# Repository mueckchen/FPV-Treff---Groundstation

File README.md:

# FPV-Treff---Groundstation
https://www.fpv-treff.de/forum/index.php?threads/eigenbau-groundstation-videosplitter.1016/#post-31431

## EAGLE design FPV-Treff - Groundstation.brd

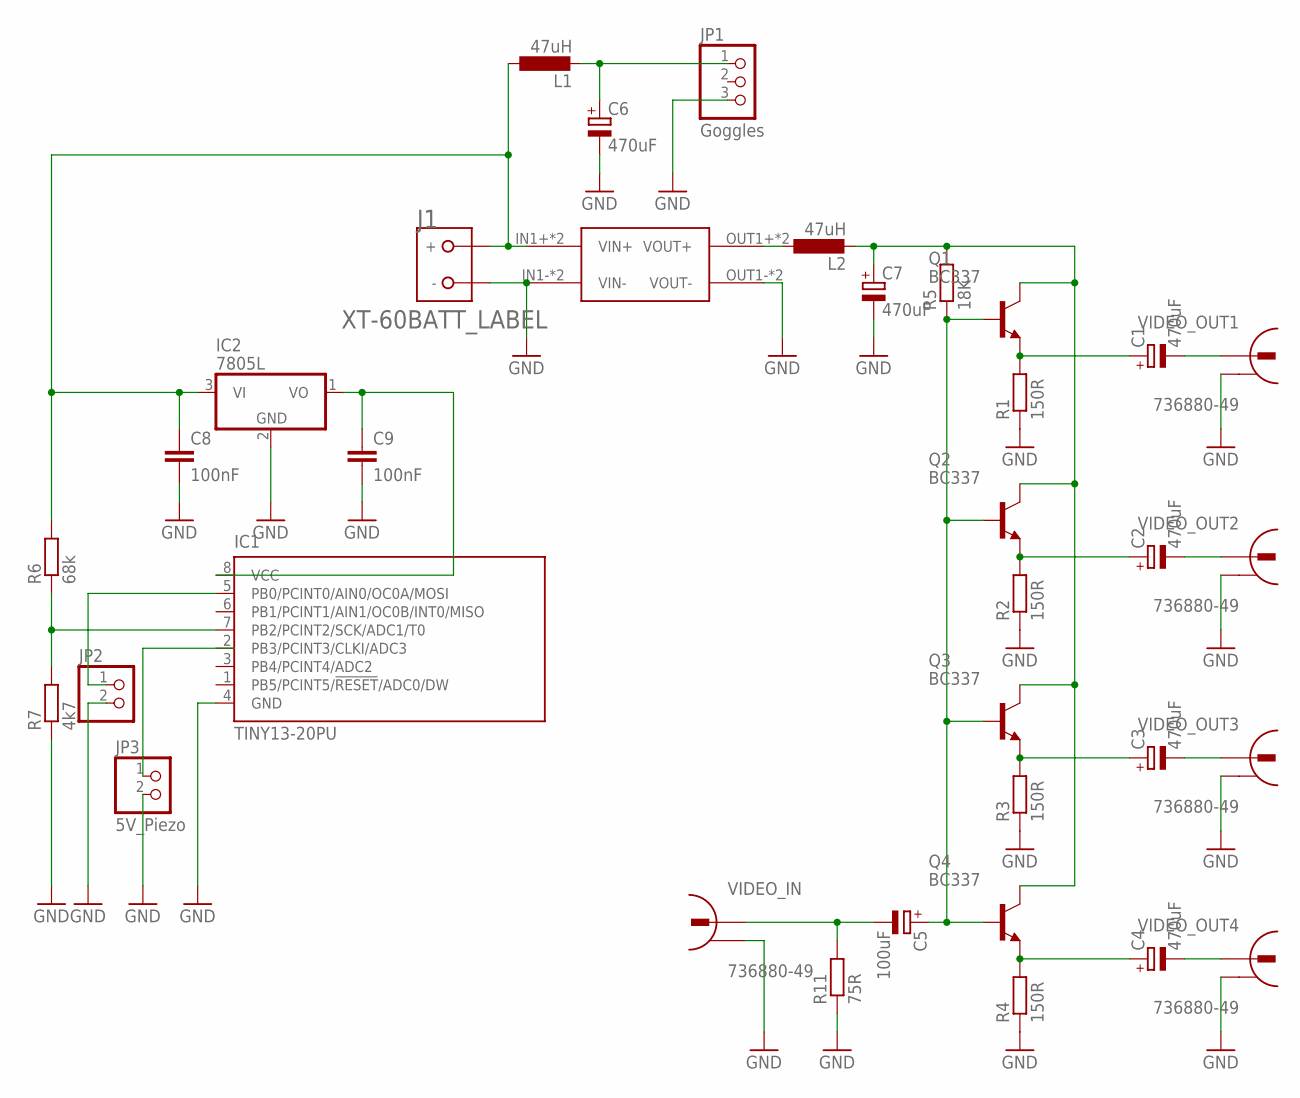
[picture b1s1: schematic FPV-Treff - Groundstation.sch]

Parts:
C1, C2, C3, C4, C6, C7: 470uF; B45181B
C5: 100uF; B45181B
C8, C9: 100nF; C025_050-025X075
IC1: TINY13-20PU; DIL08
IC2: 7805L; TO92
J1: XT-60BATT_LABEL; XT-60
JP1: Goggles; 1X03
JP2: PINHD-1X2_2.54; 1X02
JP3: 5V_Piezo; 1X02
L1, L2: 47uH; 0204V
Q1, Q2, Q3, Q4: BC337; TO92
R1, R2, R3, R4: 150R; 0204V
R5: 18K; 0204V
R6: 68k; 0207/10
R7: 4k7; 0207/10
R11: 75R; 0204V
U$1: MP1584; DC-BRICK
VIDEO_IN: 736880-49
VIDEO_OUT1, VIDEO_OUT2, VIDEO_OUT3, VIDEO_OUT4: 736880-49

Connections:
GND: C6.-, C7.-, C8.2, C9.2, IC1.4 (GND), IC2.2 (GND), J1.GND (-), JP1.3, JP2.2, JP3.2, R1.1, R2.1, R3.1, R4.1, R7.1, R11.1, U$1.IN1- (VIN-), U$1.IN2- (VIN-), U$1.OUT1- (VOUT-), U$1.OUT2- (VOUT-), VIDEO_IN.2, VIDEO_OUT1.2, VIDEO_OUT2.2, VIDEO_OUT3.2, VIDEO_OUT4.2
unnamed: C2.+, Q2.1 (E), R2.2
unnamed: C6.+, JP1.1, L1.2
unnamed: C2.-, VIDEO_OUT2.1
unnamed: C3.+, Q3.1 (E), R3.2
unnamed: C7.+, L2.2, Q1.3 (C), Q2.3 (C), Q3.3 (C), Q4.3 (C), R5.2
unnamed: C3.-, VIDEO_OUT3.1
unnamed: C8.1, IC2.3 (VI), J1.BATT (+), L1.1, R6.2, U$1.IN1+ (VIN+), U$1.IN2+ (VIN+)
unnamed: C5.-, R11.2, VIDEO_IN.1
unnamed: L2.1, U$1.OUT1+ (VOUT+), U$1.OUT2+ (VOUT+)
unnamed: IC1.5 (PB0/PCINT0/AIN0/OC0A/MOSI), JP2.1
unnamed: C9.1, IC1.8 (VCC), IC2.1 (VO)
unnamed: IC1.7 (PB2/PCINT2/SCK/ADC1/T0), R6.1, R7.2
unnamed: C1.+, Q1.1 (E), R1.2
unnamed: C4.+, Q4.1 (E), R4.2
unnamed: C5.+, Q1.2 (B), Q2.2 (B), Q3.2 (B), Q4.2 (B), R5.1
unnamed: C1.-, VIDEO_OUT1.1
unnamed: C4.-, VIDEO_OUT4.1

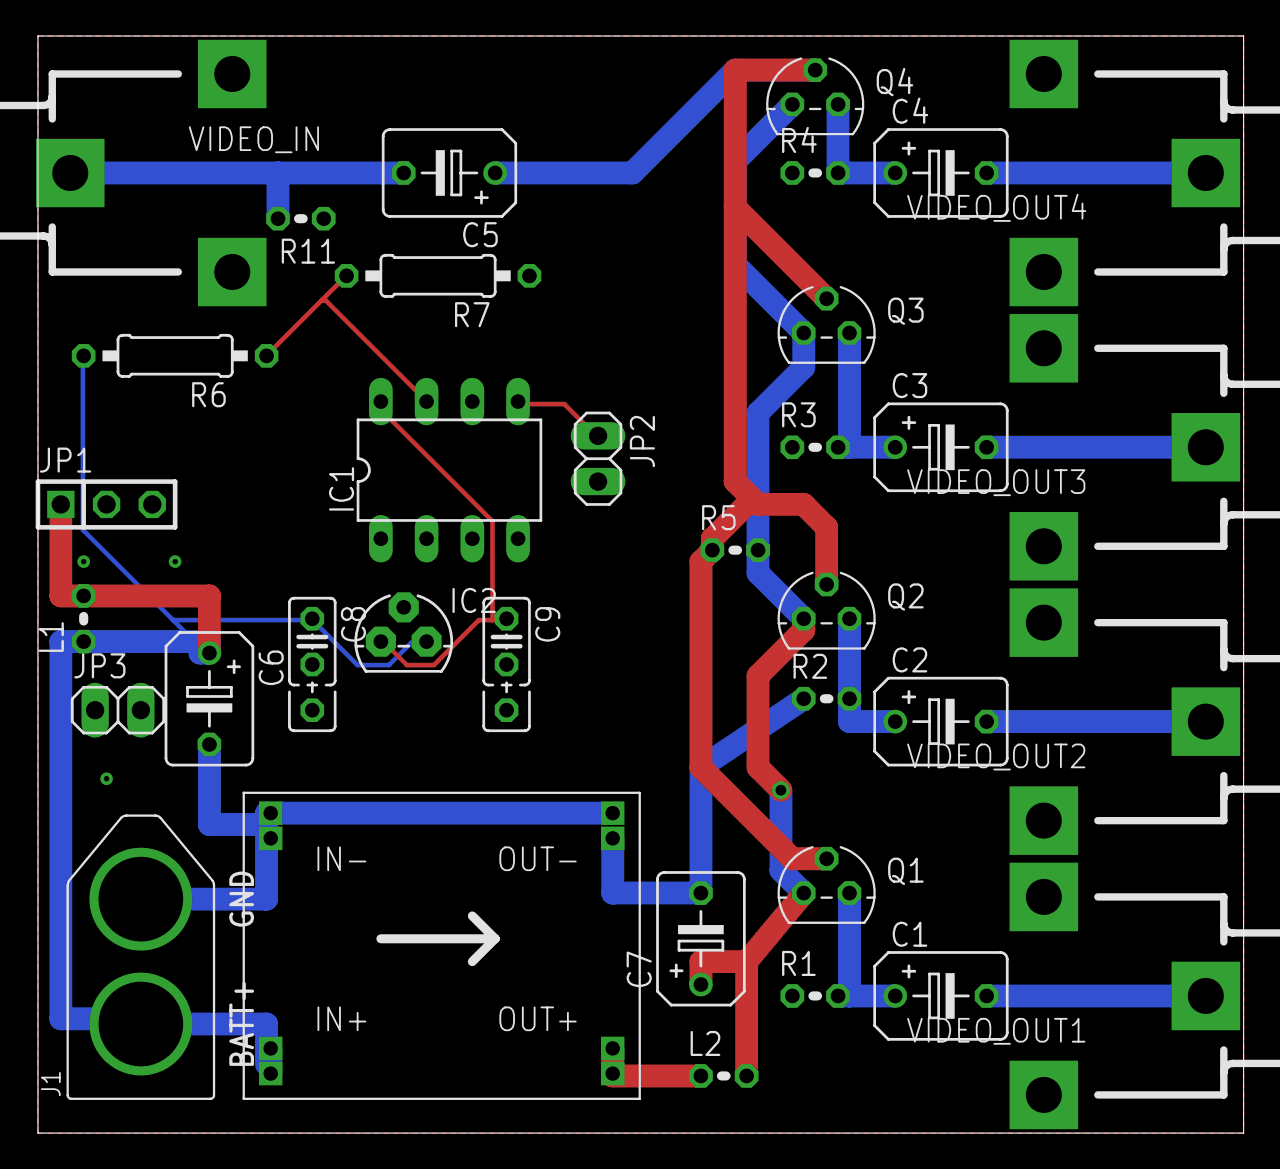
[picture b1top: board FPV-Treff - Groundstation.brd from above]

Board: 2 copper layers, 67.0 x 61.0 mm, 35 parts (0 on the bottom side), 18 nets.

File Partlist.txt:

Partlist:
Assembly variant: THT

Part       Value           Device

C1         470uF           Elektrolytkondensator/Electrolytic capacitor (5mm)
C2         470uF           Elektrolytkondensator/Electrolytic capacitor (5mm)
C3         470uF           Elektrolytkondensator/Electrolytic capacitor (5mm)
C4         470uF           Elektrolytkondensator/Electrolytic capacitor (5mm)
C5         100uF           Elektrolytkondensator/Electrolytic capacitor (5mm)
C6         470uF           Elektrolytkondensator/Electrolytic capacitor (5mm)
C7         470uF           Elektrolytkondensator/Electrolytic capacitor (5mm)
C8         100nF           Kondensator/Capacitor (2,5/5mm)
C9         100nF           Kondensator/Capacitor (2,5/5mm)
IC1        TINY13-20PU     TINY13-20PU (DIL08)
IC2        7805L           Linearregler (TO92)
J1         XT-60BATT_LABEL XT-60
JP1        Goggles         Stiftleiste/Pinheader-1X3 (2.54mm)
JP2                        Stiftleiste/Pinheader-1X2 (2.54mm)
JP3        5V_Piezo        Stiftleiste/Pinheader-1X2 (2.54mm)
L1         47uH            Spule/Coil 0204
L2         47uH            Spule/Coil 0204
Q1         BC337           Transistor (NPN) TO92
Q2         BC337           Transistor (NPN) TO92
Q3         BC337           Transistor (NPN) TO92
Q4         BC337           Transistor (NPN) TO92
R1         150R            Widerstand/Resistor 0204/0,25W
R2         150R            Widerstand/Resistor 0204/0,25W
R3         150R            Widerstand/Resistor 0204/0,25W
R4         150R            Widerstand/Resistor 0204/0,25W
R5         18K             Widerstand/Resistor 0204/0,25W
R6         68k             Widerstand/Resistor 0204/0,25W
R7         4k7             Widerstand/Resistor 0204/0,25W
R11        75R             Widerstand/Resistor 0204/0,25W
U$1        MP1584          MP1584
VIDEO_IN   736880-49       Cinch-Buchse (Mono)
VIDEO_OUT1 736880-49       Cinch-Buchse (Mono)
VIDEO_OUT2 736880-49       Cinch-Buchse (Mono)
VIDEO_OUT3 736880-49       Cinch-Buchse (Mono)
VIDEO_OUT4 736880-49       Cinch-Buchse (Mono)
